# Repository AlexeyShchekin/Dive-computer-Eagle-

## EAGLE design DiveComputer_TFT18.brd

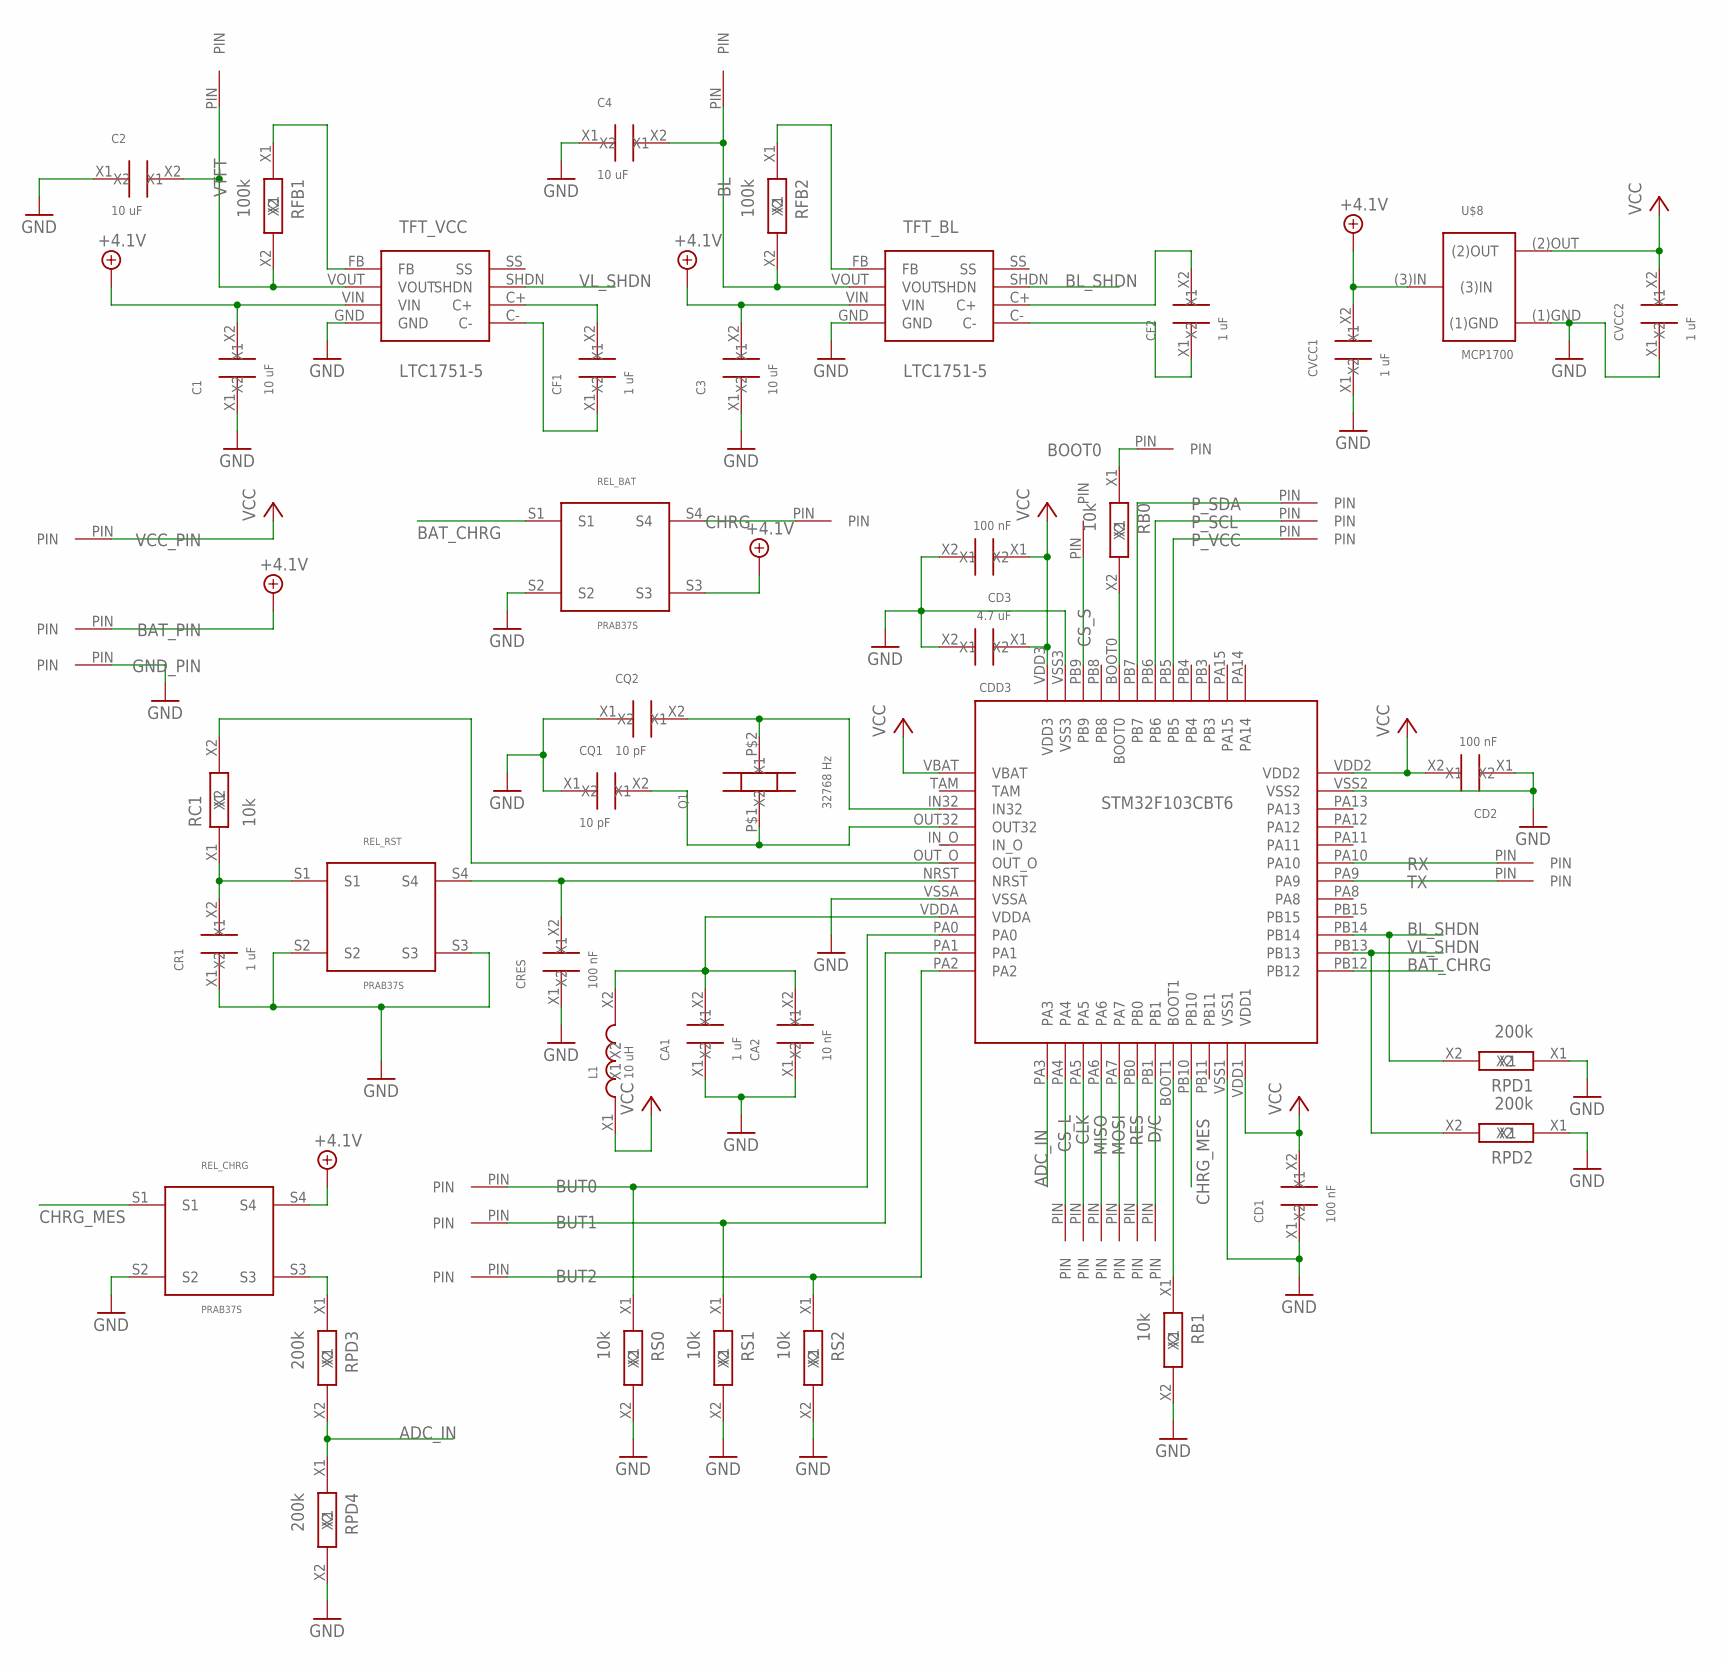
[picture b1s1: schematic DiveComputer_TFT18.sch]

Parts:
BAT_PIN: PIN_06
BL: PIN_06
BOOT0: PIN_06
BUT0, BUT1, BUT2: PIN_06
C1, C2, C3, C4: 10 uF; SMD_2.1X1.25
CA1: 1 uF; SMD_2.1X1.25
CA2: 10 nF; SMD_2.1X1.25
CD1, CD2, CD3: 100 nF; SMD_2.1X1.25
CDD3: 4.7 uF; SMD_2.1X1.25
CF1, CF2: 1 uF; SMD_2.1X1.25
CHRG: PIN_06
CLK: PIN_06
CQ1, CQ2: 10 pF; SMD_2.1X1.25
CR1: 1 uF; SMD_2.1X1.25
CRES: 100 nF; SMD_2.1X1.25
CS_L: PIN_06
CS_S: PIN_06
CVCC1, CVCC2: 1 uF; SMD_2.1X1.25
D/C: PIN_06
GND_PIN: PIN_06
L1: 10 uH; SMD_2.1X1.25
MISO: PIN_06
MOSI: PIN_06
P_SCL: PIN_06
P_SDA: PIN_06
P_VCC: PIN_06
Q1: 32768 Hz; QUARTZ_CYL
RB0, RB1: 10k; SMD_2.1X1.25
RC1: 10k; SMD_2.1X1.25
REL_BAT: PRAB37S
REL_CHRG: PRAB37S
REL_RST: PRAB37S
RES: PIN_06
RFB1, RFB2: 100k; SMD_2.1X1.25
RPD1, RPD2, RPD3, RPD4: 200k; SMD_2.1X1.25
RS0, RS1, RS2: 10k; SMD_2.1X1.25
RX: PIN_06
STM32F103CBT6: STM32F103CBT6
TFT_BL: LTC1751-5
TFT_VCC: LTC1751-5
TX: PIN_06
U$8: MCP1700
VCC_PIN: PIN_06
VTFT: PIN_06

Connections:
+4.1V: BAT_PIN.PIN, C1.X2, C3.X2, CVCC1.X2, REL_BAT.S3, REL_CHRG.S4, TFT_BL.VIN, TFT_VCC.VIN, U$8.(3)IN
ADC_IN: RPD3.X2, RPD4.X1, STM32F103CBT6.PA3
BAT_CHRG: REL_BAT.S1, STM32F103CBT6.PB12
BL_SHDN: RPD1.X2, STM32F103CBT6.PB14, TFT_BL.SHDN
CHRG_MES: REL_CHRG.S1, STM32F103CBT6.PB10
GND: C1.X1, C2.X1, C3.X1, C4.X1, CA1.X1, CA2.X1, CD1.X1, CD2.X1, CD3.X2, CDD3.X2, CQ1.X1, CQ2.X1, CR1.X1, CRES.X1, CVCC1.X1, CVCC2.X1, GND_PIN.PIN, RB1.X2, REL_BAT.S2, REL_CHRG.S2, REL_RST.S2, REL_RST.S3, RPD1.X1, RPD2.X1, RPD4.X2, RS0.X2, RS1.X2, RS2.X2, STM32F103CBT6.VSS1, STM32F103CBT6.VSS2, STM32F103CBT6.VSS3, STM32F103CBT6.VSSA, TFT_BL.GND, TFT_VCC.GND, U$8.(1)GND
unnamed: CA1.X2, CA2.X2, L1.X2, STM32F103CBT6.VDDA
unnamed: CRES.X2, REL_RST.S4, STM32F103CBT6.NRST
unnamed: RB1.X1, STM32F103CBT6.BOOT1
unnamed: CQ2.X2, Q1.P$2 (X2), STM32F103CBT6.IN32
unnamed: CQ1.X2, Q1.P$1 (X1), STM32F103CBT6.OUT32
unnamed: RB0.X2, STM32F103CBT6.BOOT0
unnamed: BOOT0.PIN, RB0.X1
unnamed: BUT2.PIN, RS2.X1, STM32F103CBT6.PA2
unnamed: BUT1.PIN, RS1.X1, STM32F103CBT6.PA1
unnamed: BUT0.PIN, RS0.X1, STM32F103CBT6.PA0
unnamed: CS_L.PIN, STM32F103CBT6.PA4
unnamed: CLK.PIN, STM32F103CBT6.PA5
unnamed: MISO.PIN, STM32F103CBT6.PA6
unnamed: MOSI.PIN, STM32F103CBT6.PA7
unnamed: RES.PIN, STM32F103CBT6.PB0
unnamed: D/C.PIN, STM32F103CBT6.PB1
unnamed: CF1.X2, TFT_VCC.C+
unnamed: CF1.X1, TFT_VCC.C-
unnamed: CF2.X2, TFT_BL.C+
unnamed: CF2.X1, TFT_BL.C-
unnamed: BL.PIN, C4.X2, RFB2.X2, TFT_BL.VOUT
unnamed: RFB2.X1, TFT_BL.FB
unnamed: C2.X2, RFB1.X2, TFT_VCC.VOUT, VTFT.PIN
unnamed: RFB1.X1, TFT_VCC.FB
unnamed: CR1.X2, RC1.X1, REL_RST.S1
unnamed: P_VCC.PIN, STM32F103CBT6.PB5
unnamed: P_SCL.PIN, STM32F103CBT6.PB6
unnamed: P_SDA.PIN, STM32F103CBT6.PB7
unnamed: CS_S.PIN, STM32F103CBT6.PB9
unnamed: STM32F103CBT6.PA9, TX.PIN
unnamed: RX.PIN, STM32F103CBT6.PA10
unnamed: REL_CHRG.S3, RPD3.X1
unnamed: RC1.X2, STM32F103CBT6.OUT_O
unnamed: CHRG.PIN, REL_BAT.S4
VCC: CD1.X2, CD2.X2, CD3.X1, CDD3.X1, CVCC2.X2, L1.X1, STM32F103CBT6.VBAT, STM32F103CBT6.VDD1, STM32F103CBT6.VDD2, STM32F103CBT6.VDD3, U$8.(2)OUT, VCC_PIN.PIN
VL_SHDN: RPD2.X2, STM32F103CBT6.PB13, TFT_VCC.SHDN

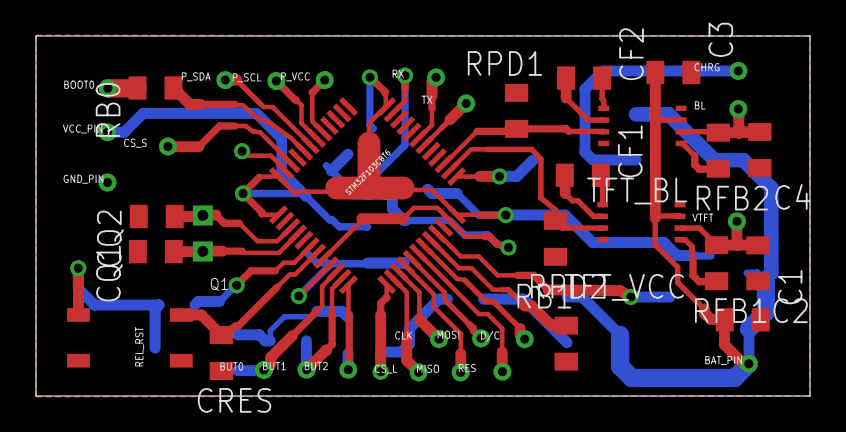
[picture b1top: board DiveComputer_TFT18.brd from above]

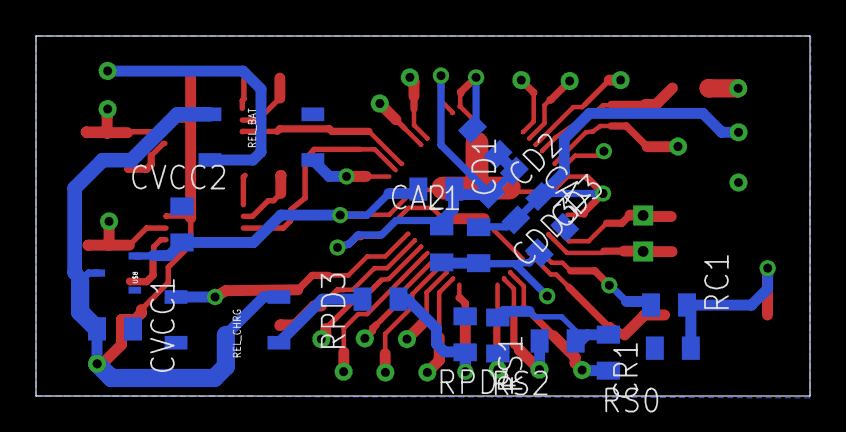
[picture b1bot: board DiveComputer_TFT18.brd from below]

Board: 2 copper layers, 43.0 x 20.0 mm, 61 parts (19 on the bottom side), 42 nets.

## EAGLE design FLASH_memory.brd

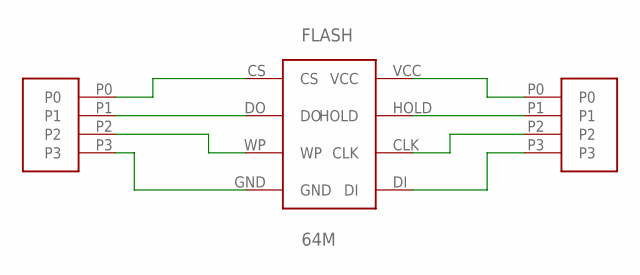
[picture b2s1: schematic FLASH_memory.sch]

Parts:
FLASH: 64M; FLASH_W25Q64FVSSIG
U$2, U$3: 4PIN

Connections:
GND: FLASH.GND, U$2.P3
unnamed: FLASH.CS, U$2.P0
unnamed: FLASH.VCC, U$3.P0
unnamed: FLASH.DO, U$2.P1
unnamed: FLASH.HOLD, U$3.P1
unnamed: FLASH.WP, U$2.P2
unnamed: FLASH.CLK, U$3.P2
unnamed: FLASH.DI, U$3.P3

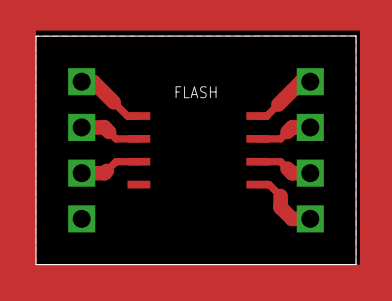
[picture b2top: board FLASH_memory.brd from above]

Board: 2 copper layers, 17.8 x 12.7 mm, 3 parts (0 on the bottom side), 8 nets.

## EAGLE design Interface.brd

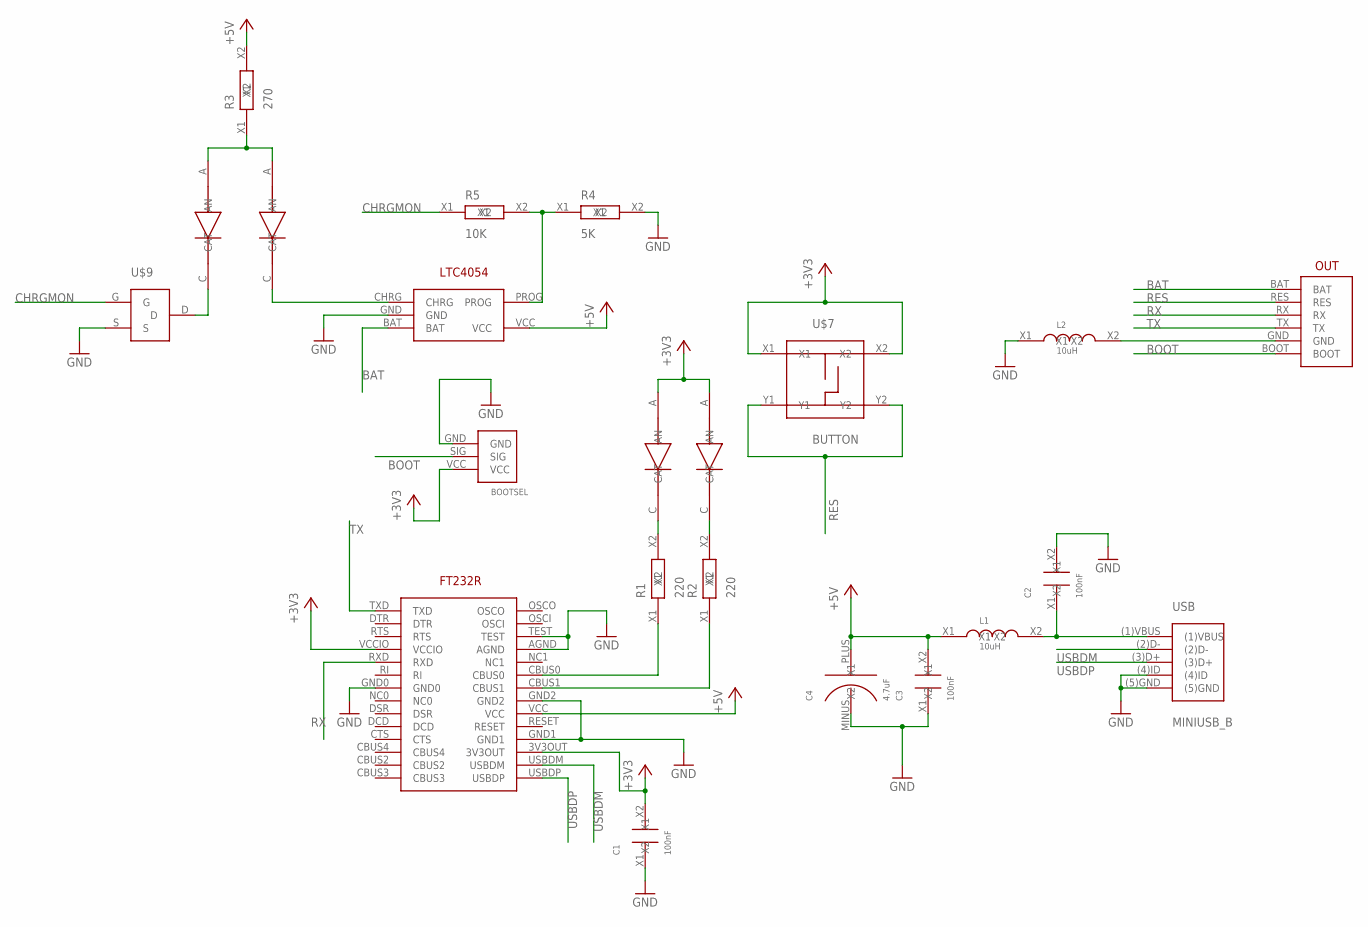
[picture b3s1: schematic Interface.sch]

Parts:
BOOTSEL: BOOT3PIN
C1, C2, C3: 100nF; SMD_2.1X1.25
C4: 4.7uF; C_SMD_TA_A
L1, L2: 10uH; SMD_2.1X1.25
R1, R2: 220; SMD_2.1X1.25
R3: 270; SMD_2.1X1.25
R4: 5K; SMD_2.1X1.25
R5: 10K; SMD_2.1X1.25
U$1: FT232R; FT232
U$2: LTC4054
U$3, U$4, U$5, U$6: LED0805
U$7: BUTTON
U$8: PLUG6PIN
U$9: IRFML8244TRPBF
USB: MINIUSB_B

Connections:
+3V3: BOOTSEL.VCC, C1.X2, U$1.3V3OUT, U$1.VCCIO, U$4.A (AN), U$6.A (AN), U$7.X1, U$7.X2
+5V: C3.X2, C4.PLUS (X2), L1.X1, R3.X2, U$1.VCC, U$2.VCC
BAT: U$2.BAT, U$8.BAT
BOOT: BOOTSEL.SIG, U$8.BOOT
CHRGMON: R5.X1, U$9.G
GND: BOOTSEL.GND, C1.X1, C2.X2, C3.X1, C4.MINUS (X1), L2.X1, R4.X2, U$1.AGND, U$1.GND0, U$1.GND1, U$1.GND2, U$1.TEST, U$2.GND, U$9.S, USB.(4)ID, USB.(5)GND
unnamed: C2.X1, L1.X2, USB.(1)VBUS
unnamed: R3.X1, U$3.A (AN), U$5.A (AN)
unnamed: R1.X2, U$4.C (CAT)
unnamed: R2.X2, U$6.C (CAT)
unnamed: R1.X1, U$1.CBUS0
unnamed: R2.X1, U$1.CBUS1
unnamed: U$2.CHRG, U$3.C (CAT)
unnamed: U$5.C (CAT), U$9.D
unnamed: L2.X2, U$8.GND
unnamed: R4.X1, R5.X2, U$2.PROG
RES: U$7.Y1, U$7.Y2, U$8.RES
RX: U$1.RXD, U$8.RX
TX: U$1.TXD, U$8.TX
USBDM: U$1.USBDM, USB.(2)D-
USBDP: U$1.USBDP, USB.(3)D+

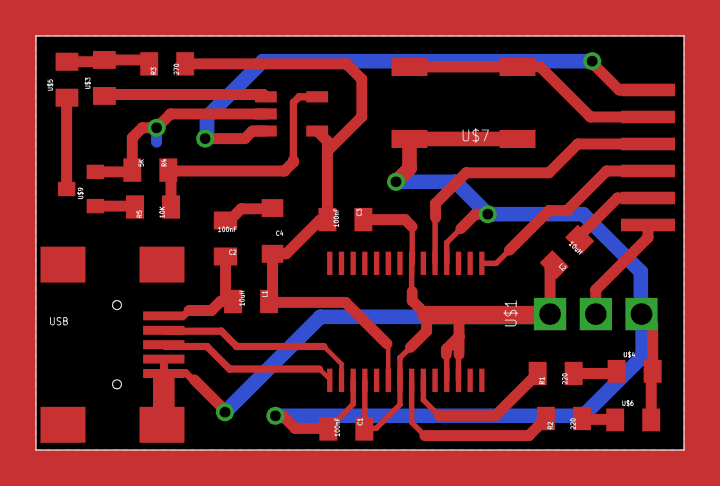
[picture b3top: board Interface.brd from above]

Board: 2 copper layers, 36.0 x 23.0 mm, 22 parts (0 on the bottom side), 21 nets.

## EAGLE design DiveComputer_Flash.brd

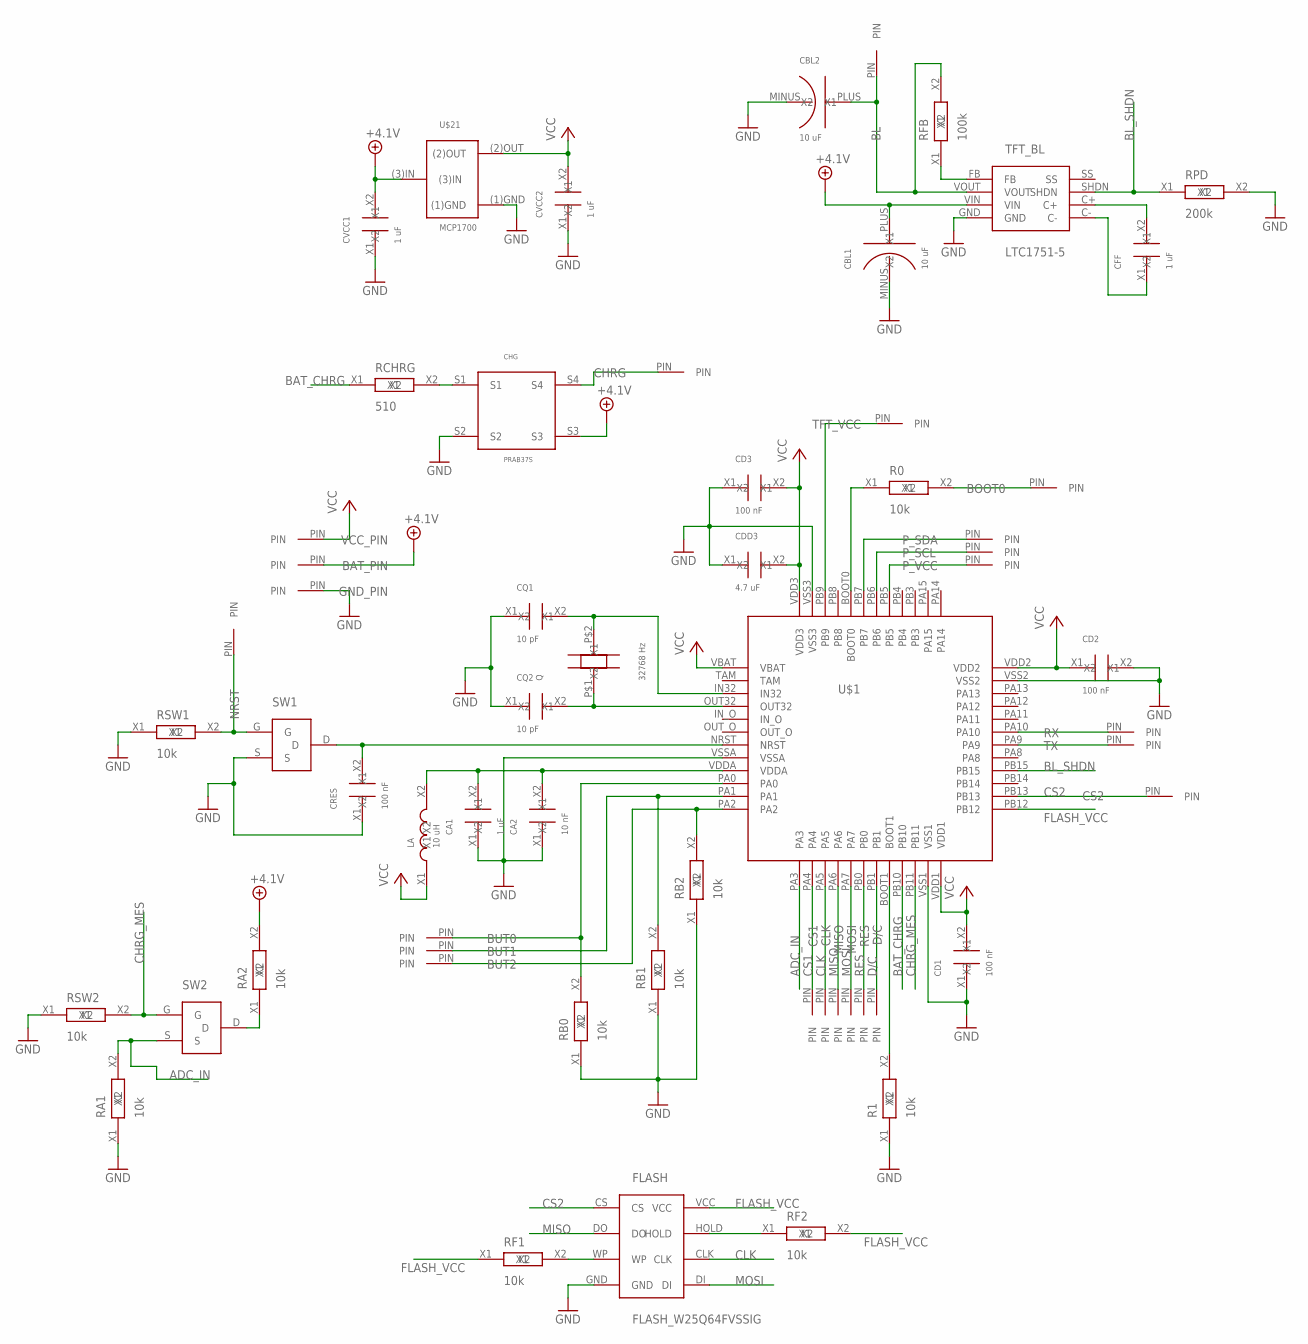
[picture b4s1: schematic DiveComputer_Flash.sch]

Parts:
BAT_PIN: PIN_06
BL: PIN_06
BOOT0: PIN_06
BUT0, BUT1, BUT2: PIN_06
CA1: 1 uF; SMD_2.1X1.25
CA2: 10 nF; SMD_2.1X1.25
CBL1, CBL2: 10 uF; C_SMD_TA_A
CD1, CD2, CD3: 100 nF; SMD_2.1X1.25
CDD3: 4.7 uF; SMD_2.1X1.25
CFF: 1 uF; SMD_2.1X1.25
CHG: PRAB37S
CHRG: PIN_06
CLK: PIN_06
CQ1, CQ2: 10 pF; SMD_2.1X1.25
CRES: 100 nF; SMD_2.1X1.25
CS1, CS2: PIN_06
CVCC1, CVCC2: 1 uF; SMD_2.1X1.25
D/C: PIN_06
FLASH: FLASH_W25Q64FVSSIG
GND_PIN: PIN_06
LA: 10 uH; SMD_2.1X1.25
MISO: PIN_06
MOSI: PIN_06
NRST: PIN_06
P_SCL: PIN_06
P_SDA: PIN_06
P_VCC: PIN_06
Q: 32768 Hz; QUARTZ_CYL
R0, R1: 10k; SMD_2.1X1.25
RA1, RA2: 10k; SMD_2.1X1.25
RB0, RB1, RB2: 10k; SMD_2.1X1.25
RCHRG: 510; SMD_2.1X1.25
RES: PIN_06
RF1, RF2: 10k; SMD_2.1X1.25
RFB: 100k; SMD_2.1X1.25
RPD: 200k; SMD_2.1X1.25
RSW1, RSW2: 10k; SMD_2.1X1.25
RX: PIN_06
SW1, SW2: IRFML8244TRPBF
TFT_BL: LTC1751-5
TFT_VCC: PIN_06
TX: PIN_06
U$1: STM32F103CBT6
U$21: MCP1700
VCC_PIN: PIN_06

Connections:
+4.1V: BAT_PIN.PIN, CBL1.PLUS (X2), CHG.S3, CVCC1.X2, RA2.X2, TFT_BL.VIN, U$21.(3)IN
ADC_IN: RA1.X2, SW2.S, U$1.PA3
BAT_CHRG: RCHRG.X1, U$1.PB10
BL_SHDN: RPD.X1, TFT_BL.SHDN, U$1.PB15
CHRG_MES: RSW2.X2, SW2.G, U$1.PB11
CLK: CLK.PIN, FLASH.CLK, U$1.PA5
CS1: CS1.PIN, U$1.PA4
CS2: CS2.PIN, FLASH.CS, U$1.PB13
D/C: D/C.PIN, U$1.PB1
FLASH_VCC: FLASH.VCC, RF1.X1, RF2.X2, U$1.PB12
GND: CA1.X1, CA2.X1, CBL1.MINUS (X1), CBL2.MINUS (X1), CD1.X1, CD2.X2, CD3.X1, CDD3.X1, CHG.S2, CQ1.X1, CQ2.X1, CRES.X1, CVCC1.X1, CVCC2.X1, FLASH.GND, GND_PIN.PIN, R1.X1, RA1.X1, RB0.X1, RB1.X1, RB2.X1, RPD.X2, RSW1.X1, RSW2.X1, SW1.S, TFT_BL.GND, U$1.VSS1, U$1.VSS2, U$1.VSS3, U$1.VSSA, U$21.(1)GND
MISO: FLASH.DO, MISO.PIN, U$1.PA6
MOSI: FLASH.DI, MOSI.PIN, U$1.PA7
unnamed: R0.X1, U$1.BOOT0
unnamed: BOOT0.PIN, R0.X2
unnamed: P_VCC.PIN, U$1.PB5
unnamed: P_SCL.PIN, U$1.PB6
unnamed: P_SDA.PIN, U$1.PB7
unnamed: RX.PIN, U$1.PA10
unnamed: TX.PIN, U$1.PA9
unnamed: CQ1.X2, Q.P$2 (X2), U$1.IN32
unnamed: R1.X2, U$1.BOOT1
unnamed: CQ2.X2, Q.P$1 (X1), U$1.OUT32
unnamed: CRES.X2, SW1.D, U$1.NRST
unnamed: NRST.PIN, RSW1.X2, SW1.G
unnamed: CA1.X2, CA2.X2, LA.X2, U$1.VDDA
unnamed: BUT0.PIN, RB0.X2, U$1.PA0
unnamed: BUT1.PIN, RB1.X2, U$1.PA1
unnamed: BUT2.PIN, RB2.X2, U$1.PA2
unnamed: CHG.S4, CHRG.PIN
unnamed: CHG.S1, RCHRG.X2
unnamed: FLASH.WP, RF1.X2
unnamed: FLASH.HOLD, RF2.X1
unnamed: RA2.X1, SW2.D
unnamed: CFF.X2, TFT_BL.C+
unnamed: CFF.X1, TFT_BL.C-
unnamed: RFB.X1, TFT_BL.FB
unnamed: BL.PIN, CBL2.PLUS (X2), RFB.X2, TFT_BL.VOUT
unnamed: TFT_VCC.PIN, U$1.PB9
RES: RES.PIN, U$1.PB0
VCC: CD1.X2, CD2.X1, CD3.X2, CDD3.X2, CVCC2.X2, LA.X1, U$1.VBAT, U$1.VDD1, U$1.VDD2, U$1.VDD3, U$21.(2)OUT, VCC_PIN.PIN

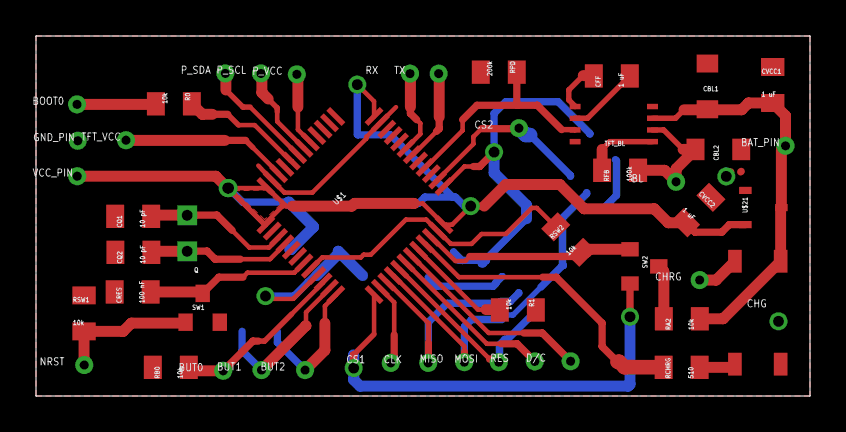
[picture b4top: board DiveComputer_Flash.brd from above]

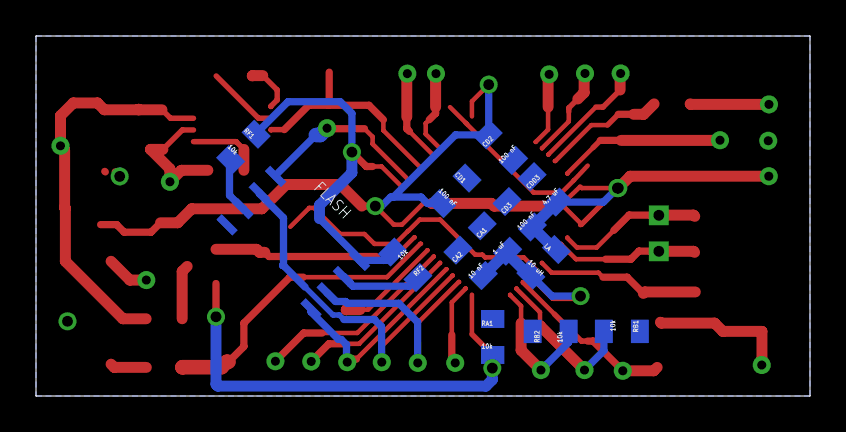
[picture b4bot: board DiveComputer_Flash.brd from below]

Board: 2 copper layers, 43.0 x 20.0 mm, 60 parts (13 on the bottom side), 41 nets.
